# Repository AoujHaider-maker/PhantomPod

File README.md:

# PhantomPod!
Concept illustration:

PhantomPod is a pocket digital cassette player built around an ESP32-S3. You slot in a vertical cassette-shaped cartridge that holds a microSD card and an NFC tag. Spring-loaded pogo pins read its six gold contacts, and the player recognizes it automatically. It has a 2.23" 128×32 OLED, 12 underglow RGB LEDs, a side rotary encoder and buttons, two headphone jacks driven by a PCM5102A DAC and TPA6132A2 amp, and USB-C LiPo charging. I designed the whole 80×125 mm 2-layer PCB in KiCad (schematic, layout, DRC/ERC clean), exported the Gerbers and BOM, and wrote a PlatformIO bring-up firmware starter. It hasn’t been built yet, so the firmware is untested on hardware.

## Features:

- Swapable digital cassette: vertical cassette-shaped cartridge that houses a microSD card and NFC tag internally. Slot it in, and the player will recognize it automatically.
- Pogo pin spring-loaded contact reads 6 gold contacts of the cassette analogously to how the contact mechanism would work in a standard cassette deck.
- ESP32-S3-WROOM-1 module as an “brain” placed onto 2-layer KiCad custom-made PCB (80×125 mm).
- 2.23" 128x32 OLED (I2C) for track info and animations, framed by an angled bezel so it fits the cassette-player look.
- 12 SK6812MINI RGB LED lights for the circuit under the board through the transparent shell.
- Rotary encoder on the side of the device to control volume (Bourns PEC09).
- Buttons to the side of the device for play/pause and FF/RW functions, plus one button for setup and power slider, so the front of the housing remains pristine.
- 2× 3.5 mm audio jacks, so the experience can be shared with someone else powered by PCM5102A DAC and TPA6132A2 headphone amplifier.
- Rechargeable LiPo battery charged through USB-C port, with appropriate charging circuitry and protection.
- Translucent shell inspired by Sony TPS-L2.
  
## CAD Model:

Design target: a clear shell roughly 88 × 133.5 mm and about 20 mm thick, so the board and underglow LEDs are visible. The cassette slides in vertically from the top and the pogo pins touch its six gold pads. The OLED sits behind an angled window; the display is rectangular, and the bezel plus the firmware (which keeps the corners black) give it the angled shape. The casing isn’t modelled yet. The board’s 3D model is in CAD/ for anyone designing one.

## PCB
Here's the PCB I made in  KiCad.

## Firmware Overview

Starter bring-up firmware (PlatformIO, ESP32-S3). It checks the OLED, LEDs, RC522, cassette microSD, audio and controls. Pins are in Firmware/include/pins.h. It has not been tested on hardware yet, because the board hasn’t been built. Music playback and the menu are still to do. Anyone building this is welcome to write their own firmware.

## BOM:

Here should be everything you need to make the PhantomPod. The full KiCad parts list is in Production/DCD.csv.

**Main parts**
- 1x ESP32-S3-WROOM-1-N16 module
- 1x 2.23" 128x32 I2C OLED display (4-pin: GND, VCC, SCL, SDA)
- 1x RC522 RFID reader module (8-pin)
- 1x PCM5102A DAC breakout (6-pin)
- 1x TPA6132A2 headphone amplifier
- 12x SK6812MINI RGB LEDs (underglow)
- 1x Bourns PEC09 rotary encoder (side volume dial)
- 2x CUI SJ1-3523N 3.5 mm headphone jacks
- 1x USB-C receptacle (GCT USB4105)
- 1x 3.7 V LiPo battery with protection circuit, JST-PH 2-pin plug
- 1x JST-PH S2B-PH-K 2-pin battery connector

**Cassette**
- 6x spring-loaded pogo pins (2.54 mm pitch)
- 1x NFC tag (NTAG213/215) and 1x microSD card
- 1x 3D-printed cassette and clear shell

**Power and protection**
- 1x MCP73831 LiPo charger
- 1x AP2112K-3.3 LDO regulator
- 1x USBLC6-2SC6 USB protection
- 3x AO3401A P-MOSFETs, 2x 2N7002 N-MOSFETs

**Buttons**
- 6x Omron B3U-3000P side buttons (play, forward, back, setup, reset, boot)
- 1x SPDT slide switch (power)

**Passives (0603 unless noted)**
- Capacitors: 12x 100 nF, 6x 1 uF, 1x 10 uF, 1x 0.1 uF, 3x 2.2 uF (0805), 2x 4.7 uF (0805), 1x 10 uF (0805), 1x 100 uF (1210)
- Resistors: 4x 100 kOhm, 2x 10 kOhm, 2x 5.1 kOhm, 1x 2 kOhm, 1x 1 kOhm, 1x 330 Ohm
- 1x red or green LED (charge indicator)
- Female pin sockets for the modules (1x4, 1x8, 1x6, 1x3) and a 1x6 pin header
## IMPORTANT
This is a design that hasn’t been built yet.

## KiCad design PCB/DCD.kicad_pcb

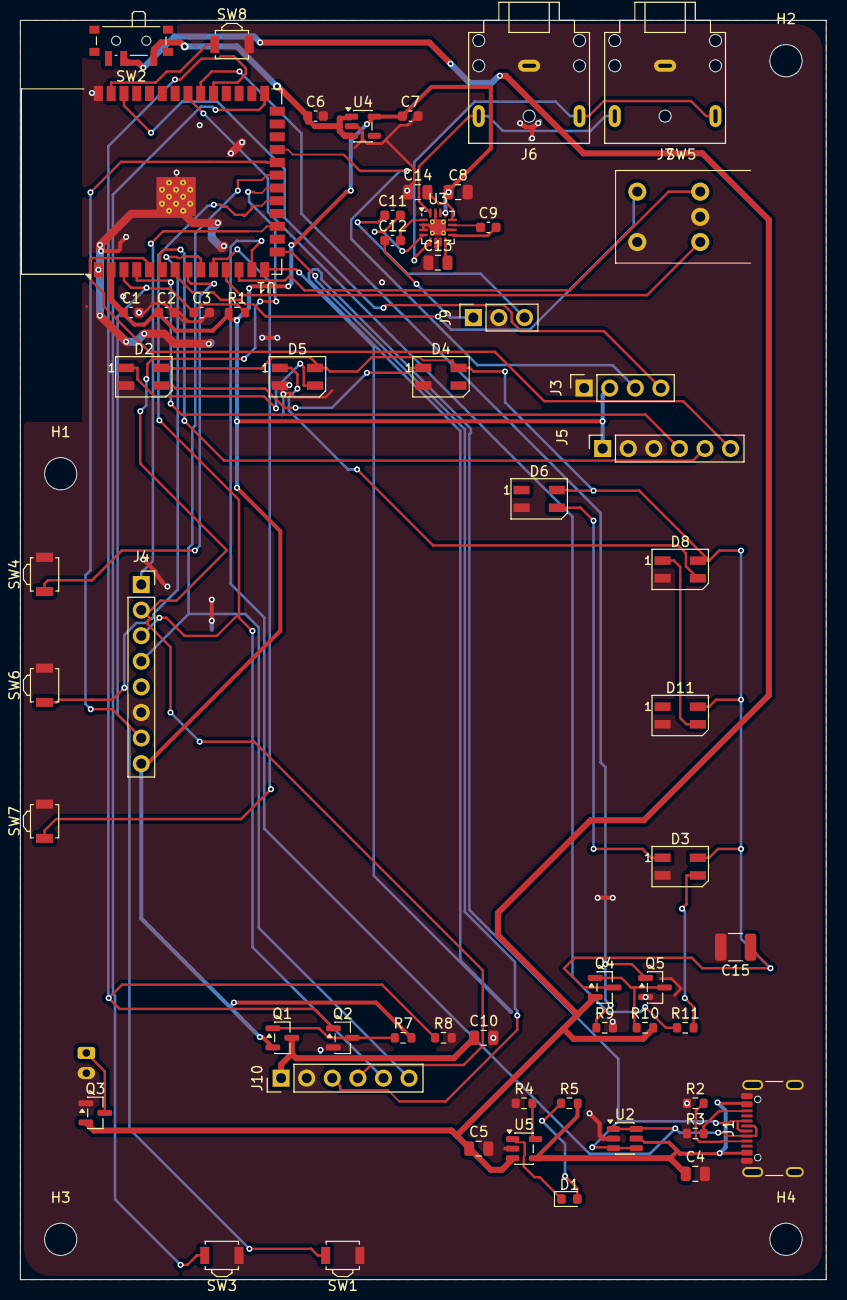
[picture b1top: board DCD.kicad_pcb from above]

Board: 2 copper layers, 80.0 x 125.0 mm, 64 parts (1 on the bottom side), 56 nets.

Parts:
BT1: Battery_Cell; JST_PH_S2B-PH-K_1x02_P2.00mm_Horizontal
C1: 10uF; C_0603_1608Metric
C2: 0.1uF; C_0603_1608Metric
C3, C6, C7, C9, C11, C12: 1uF; C_0603_1608Metric
C4, C5: 4.7uF; C_0805_2012Metric
C8, C13, C14: 2.2uF; C_0805_2012Metric
C10: 10 µF; C_0805_2012Metric
C15: 100 µF; C_1210_3225Metric
D1: LED; LED_0603_1608Metric
D2, D3, D4, D5, D6, D8, D11: SK6812MINI; LED_SK6812MINI_PLCC4_3.5x3.5mm_P1.75mm
H1, H2, H3, H4: MountingHole; MountingHole_3.2mm_M3
J1: USB_C_Receptacle_USB2.0_16P; USB_C_Receptacle_GCT_USB4105-xx-A_16P_TopMnt_Horizontal
J3: Conn_01x04; PinSocket_1x04_P2.54mm_Vertical
J4: Conn_01x08; PinSocket_1x08_P2.54mm_Vertical
J5: Conn_01x06; PinSocket_1x06_P2.54mm_Vertical
J6, J7: AudioJack3; Jack_3.5mm_CUI_SJ1-3523N_Horizontal
J9: Conn_01x03; PinSocket_1x03_P2.54mm_Vertical
J10: Conn_01x06; PinHeader_1x06_P2.54mm_Vertical
Q1, Q3, Q4: AO3401A; SOT-23
Q2, Q5: 2N7002; SOT-23
R1: 10k; R_0603_1608Metric
R2, R3: 5.1k; R_0603_1608Metric
R4: 2k; R_0603_1608Metric
R5: 1k; R_0603_1608Metric
R7, R8, R9, R10: 100 kΩ; R_0603_1608Metric
R11: 330; R_0603_1608Metric
SW1: RESET; SW_SPST_B3U-3000P
SW2: SW_SPDT; SW_SPDT_PCM12
SW3: BOOT; SW_SPST_B3U-3000P
SW4: FF; SW_SPST_B3U-3000P
SW5: RotaryEncoder_Switch; RotaryEncoder_Bourns_Horizontal_PEC09-2xxxF-Sxxxx
SW6: BACK; SW_SPST_B3U-3000P
SW7: PLAY; SW_SPST_B3U-3000P
SW8: SETUP; SW_SPST_B3U-3000P
U1: ESP32-S3-WROOM-1
U2: USBLC6-2SC6; SOT-23-6
U3: TPA6132A2RTE; WQFN-16-1EP_3x3mm_P0.5mm_EP1.6x1.6mm_ThermalVias
U4: AP2112K-3.3; SOT-23-5
U5: MCP73831-2-OT; SOT-23-5

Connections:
+3V3: C1.1, C2.1, C7.1, C8.1, J3.2, J4.8, J5.1, Q1.2 (S), R1.1, R7.2, U1.2 (3V3), U3.13 (EN), U3.14 (VDD), U4.5 (VOUT)
+5V: C4.1, J1.A4 (VBUS), J1.A9 (VBUS), J1.B4 (VBUS), J1.B9 (VBUS), R5.2, U2.5 (VBUS), U5.4 (V_{DD})
/BTN_BACK: SW6.1, U1.9 (IO16)
/BTN_FF: SW4.1, U1.8 (IO15)
/BTN_PLAY: SW7.1, U1.10 (IO17)
/BTN_SETUP: SW8.1, U1.39 (IO1)
/CASS_3V3: C10.1, J10.1, Q1.3 (D)
/CASS_CS: J10.3, U1.15 (IO3)
/CASS_EN: Q2.1 (G), R8.1, U1.31 (IO38)
/DAC_L: C12.1, J9.1
/DAC_R: C11.1, J9.3
/DATA_1: D3.1 (DOUT), D6.3 (DIN)
/DATA_8: D2.3 (DIN), D4.1 (DOUT)
/DATA_9: D2.1 (DOUT), D5.3 (DIN)
/DATA_10: D5.1 (DOUT), D8.3 (DIN)
/DATA_11: D8.1 (DOUT), D11.3 (DIN)
/ENC_A: SW5.A, U1.11 (IO18)
/ENC_B: SW5.B, U1.12 (IO8)
/ENC_SW: SW5.S2, U1.7 (IO7)
/HP_L: J6.T, J7.T, U3.16 (OUTL)
/HP_R: J6.R, J7.R, U3.5 (OUTR)
/I2C_SCL: J3.3, U1.23 (IO21)
/I2C_SDA: J3.4, U1.38 (IO2)
/I2S_BCLK: J5.4, U1.4 (IO4)
/I2S_DOUT: J5.5, U1.6 (IO6)
/I2S_WS: J5.6, U1.5 (IO5)
/LED_DATA: R11.1, U1.33 (IO40)
/LED_EN: Q5.1 (G), R9.1, U1.32 (IO39)
/LED_PWR: C15.1, D2.4 (VDD), D3.4 (VDD), D4.4 (VDD), D5.4 (VDD), D6.4 (VDD), D8.4 (VDD), D11.4 (VDD), Q4.3 (D)
/RFID_CS: J4.1, U1.17 (IO9)
/RFID_RST: J4.7, U1.22 (IO14)
/SPI_MISO: J4.4, J10.6, U1.21 (IO13)
/SPI_MOSI: J4.3, J10.5, U1.19 (IO11)
/SPI_SCK: J4.2, J10.4, U1.20 (IO12)
/USB_DM: J1.A7 (D-), J1.B7 (D-), U1.13 (USB_D-), U2.1 (I/O1), U2.6 (I/O1)
/USB_DP: J1.A6 (D+), J1.B6 (D+), U1.14 (USB_D+), U2.3 (I/O2), U2.4 (I/O2)
/VBAT: C5.1, Q3.2 (S), Q4.2 (S), R10.2, SW2.2 (B), U5.3 (V_{BAT})
/VBAT_SW: C6.1, SW2.1 (A), U4.1 (VIN), U4.3 (EN)
GND: BT1.2 (-), C1.2, C2.2, C3.2, C4.2, C5.2, C6.2, C7.2, C8.2, C10.2, C13.1, C14.1, C15.2, D2.2 (VSS), D3.2 (VSS), D4.2 (VSS), D5.2 (VSS), D6.2 (VSS), D8.2 (VSS), D11.2 (VSS), J1.A1 (GND), J1.A12 (GND), J1.B1 (GND), J1.B12 (GND), J1.SH (SHIELD), J3.1, J4.6, J5.2, J5.3, J6.S, J7.S, J9.2, J10.2, Q2.2 (S), Q3.1 (G), Q5.2 (S), R2.1, R3.1, R4.1, R8.2, R9.2, SW1.1, SW3.1, SW4.2, SW5.C, SW5.S1, SW6.2, SW7.2, SW8.2, U1.1 (GND), U1.40 (GND), U1.41 (GND), U2.2 (GND), U3.2 (INL+), U3.3 (INR+), U3.6 (G0), U3.7 (G1), U3.10 (PGND), U3.15 (SGND), U3.17 (EP), U4.2 (GND), U5.2 (V_{SS})
unnamed: BT1.1 (+), Q3.3 (D)
unnamed: D1.2 (A), R5.1
unnamed: D1.1 (K), U5.1 (STAT)
unnamed: D3.3 (DIN), R11.2
unnamed: J1.A5 (CC1), R2.2
unnamed: J1.B5 (CC2), R3.2
unnamed: Q1.1 (G), Q2.3 (D), R7.1
unnamed: Q4.1 (G), Q5.3 (D), R10.1
unnamed: C3.1, R1.2, SW1.2, U1.3 (EN)
unnamed: SW3.2, U1.27 (IO0)
unnamed: C9.2, U3.9 (CPN)
unnamed: C9.1, U3.11 (CPP)
unnamed: C14.2, U3.12 (HPVDD)
unnamed: C13.2, U3.8 (HPVSS)
unnamed: C12.2, U3.1 (INL-)
unnamed: C11.2, U3.4 (INR-)
unnamed: R4.2, U5.5 (PROG)

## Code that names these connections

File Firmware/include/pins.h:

#pragma once
// PhantomPod GPIO map. Taken from DCD.kicad_pcb (U1 = ESP32-S3-WROOM-1).
// Module pin -> GPIO is from the ESP32-S3-WROOM-1 datasheet.

// I2S -> PCM5102A (J5)
#define PIN_I2S_BCLK   4   // module pin 4
#define PIN_I2S_WS     5   // module pin 5  (LCK)
#define PIN_I2S_DOUT   6   // module pin 6  (DIN)

// Encoder + buttons (assumed wired to GND when pressed: use INPUT_PULLUP)
#define PIN_ENC_SW     7
#define PIN_ENC_A     18
#define PIN_ENC_B      8
#define PIN_BTN_FF    15
#define PIN_BTN_BACK  16
#define PIN_BTN_PLAY  17
#define PIN_BTN_SETUP  1

// USB (native, handled by the chip)
#define PIN_USB_DM    19
#define PIN_USB_DP    20

// Shared SPI bus (RC522 on J4 + cassette microSD on J10)
#define PIN_SPI_MOSI  11
#define PIN_SPI_SCK   12
#define PIN_SPI_MISO  13
#define PIN_RFID_CS    9
#define PIN_RFID_RST  14
#define PIN_CASS_CS    3   // cassette microSD chip select (J10 pin 3)
// SD_CS (GPIO10) is routed to nothing on this board revision.

// I2C OLED (J3)
#define PIN_I2C_SDA    2
#define PIN_I2C_SCL   21

// Power switches (active HIGH)
#define PIN_CASS_EN   38   // HIGH = power the cassette pads (CASS_3V3)
#define PIN_LED_EN    39   // HIGH = power the LED strip (LED_PWR)
#define PIN_LED_DATA  40   // SK6812MINI data
#define NUM_LEDS      12
